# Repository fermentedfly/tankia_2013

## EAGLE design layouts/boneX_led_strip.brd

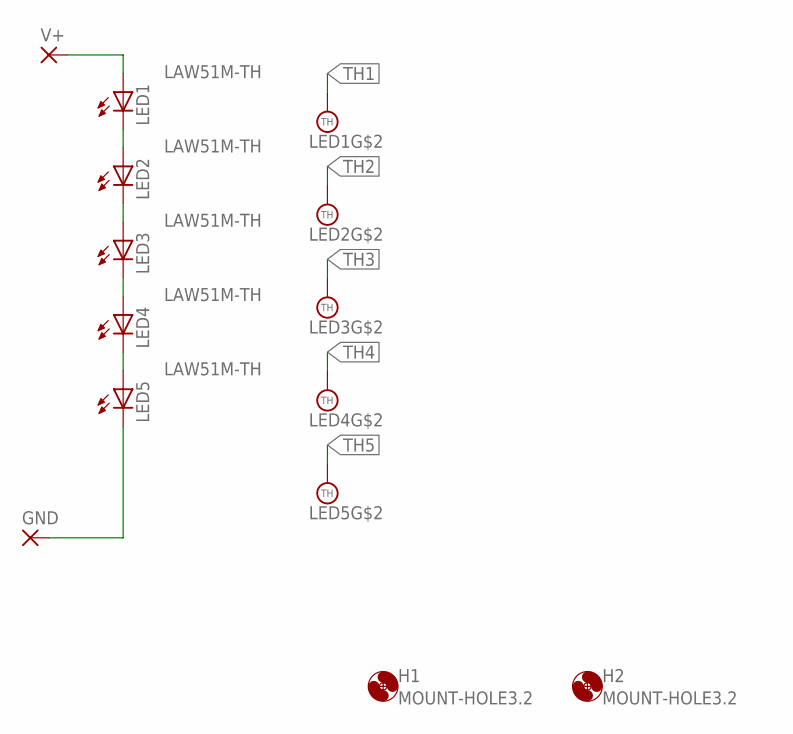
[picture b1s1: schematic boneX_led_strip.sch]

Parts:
GND: SMD5; SMD2,54-5,08
H1, H2: MOUNT-HOLE3.2; 3,2
LED1, LED2, LED3, LED4, LED5: LAW51M-TH; W51-COOL
V+: SMD5; SMD2,54-5,08

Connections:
GND: GND.1, LED5.C
unnamed: LED4.C, LED5.A
unnamed: LED3.C, LED4.A
unnamed: LED2.C, LED3.A
unnamed: LED1.C, LED2.A
TH1: LED1.TH@1 (TH), LED1.TH@2 (TH), LED1.TH@3 (TH), LED1.TH@4 (TH), LED1.TH@5 (TH), LED1.TH@6 (TH), LED1.TH@7 (TH), LED1.TH@8 (TH), LED1.TH@9 (TH), LED1.TH@10 (TH), LED1.TH@11 (TH), LED1.TH@12 (TH)
TH2: LED2.TH@1 (TH), LED2.TH@2 (TH), LED2.TH@3 (TH), LED2.TH@4 (TH), LED2.TH@5 (TH), LED2.TH@6 (TH), LED2.TH@7 (TH), LED2.TH@8 (TH), LED2.TH@9 (TH), LED2.TH@10 (TH), LED2.TH@11 (TH), LED2.TH@12 (TH)
TH3: LED3.TH@1 (TH), LED3.TH@2 (TH), LED3.TH@3 (TH), LED3.TH@4 (TH), LED3.TH@5 (TH), LED3.TH@6 (TH), LED3.TH@7 (TH), LED3.TH@8 (TH), LED3.TH@9 (TH), LED3.TH@10 (TH), LED3.TH@11 (TH), LED3.TH@12 (TH)
TH4: LED4.TH@1 (TH), LED4.TH@2 (TH), LED4.TH@3 (TH), LED4.TH@4 (TH), LED4.TH@5 (TH), LED4.TH@6 (TH), LED4.TH@7 (TH), LED4.TH@8 (TH), LED4.TH@9 (TH), LED4.TH@10 (TH), LED4.TH@11 (TH), LED4.TH@12 (TH)
TH5: LED5.TH@1 (TH), LED5.TH@2 (TH), LED5.TH@3 (TH), LED5.TH@4 (TH), LED5.TH@5 (TH), LED5.TH@6 (TH), LED5.TH@7 (TH), LED5.TH@8 (TH), LED5.TH@9 (TH), LED5.TH@10 (TH), LED5.TH@11 (TH), LED5.TH@12 (TH)
V+: LED1.A, V+.1

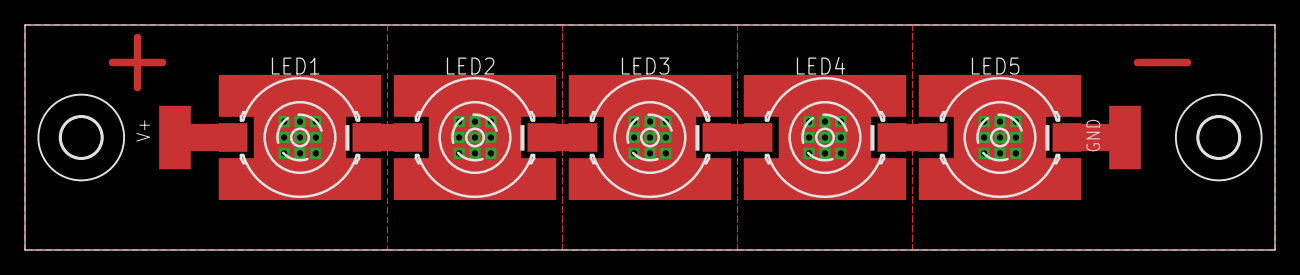
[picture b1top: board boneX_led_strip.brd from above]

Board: 2 copper layers, 100.0 x 18.0 mm, 9 parts (0 on the bottom side), 11 nets.

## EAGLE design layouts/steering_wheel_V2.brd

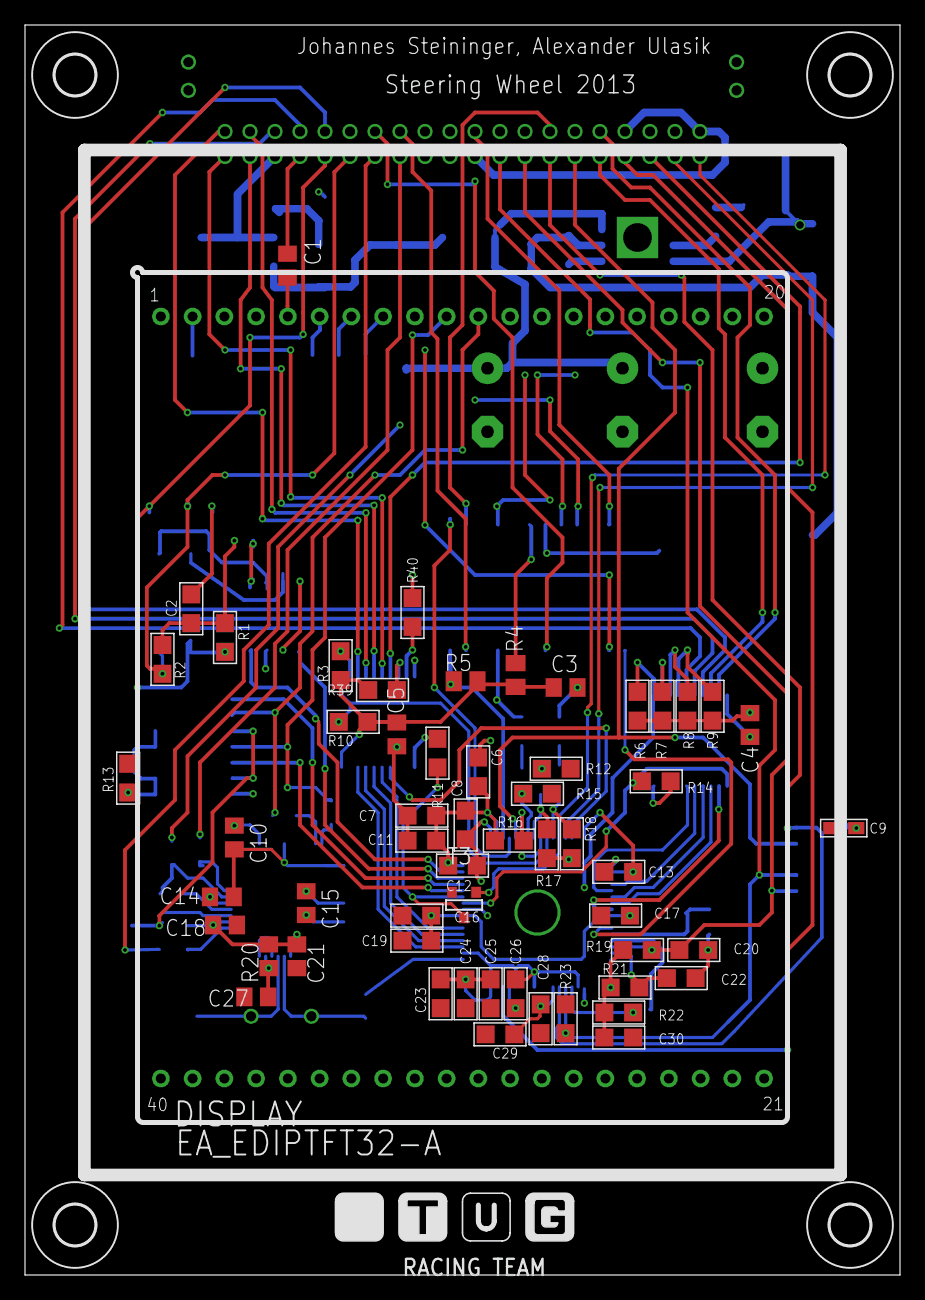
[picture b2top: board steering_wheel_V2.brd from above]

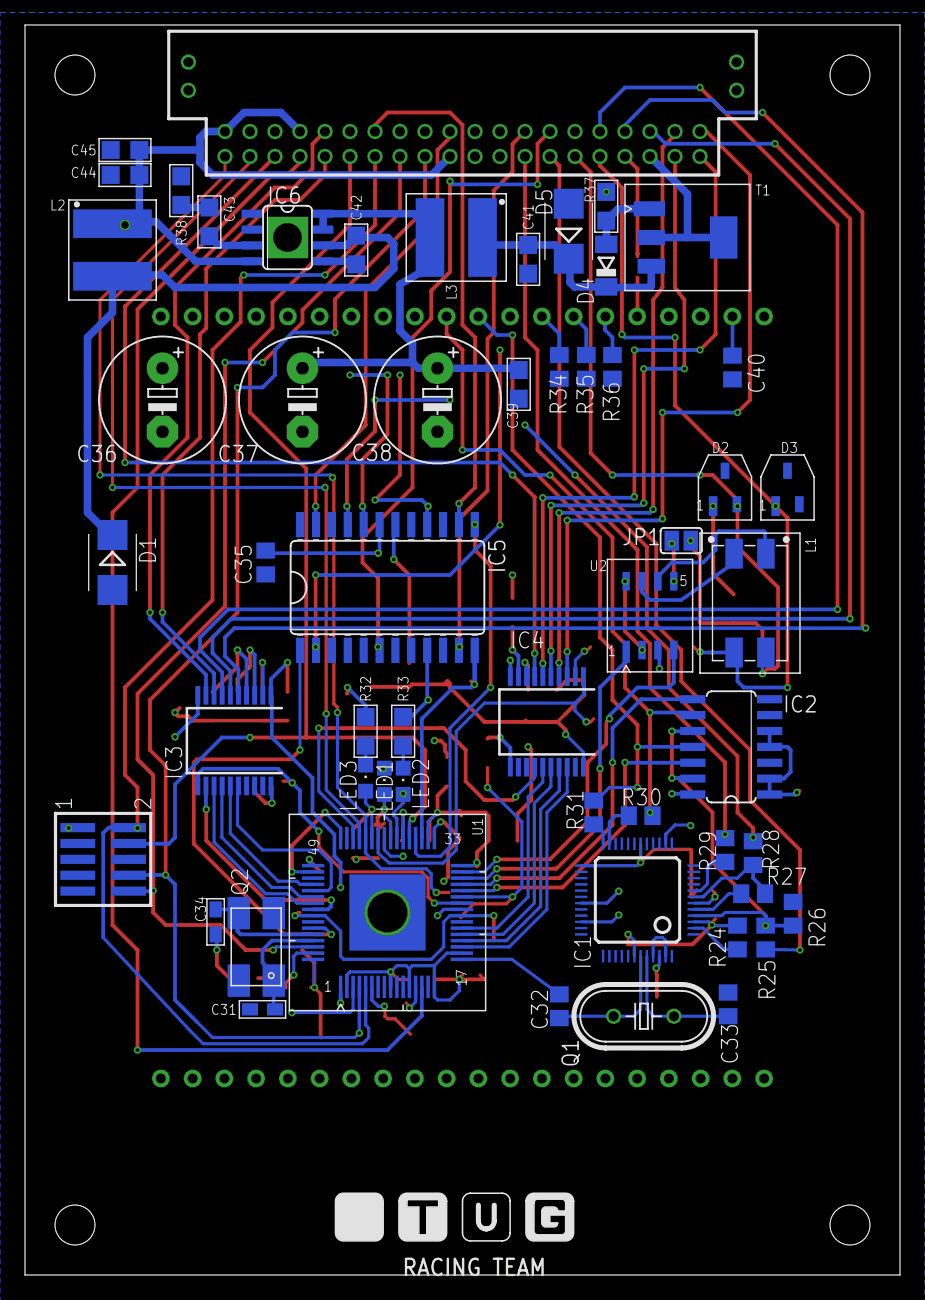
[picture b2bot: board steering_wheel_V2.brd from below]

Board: 4 copper layers, 70.0 x 100.0 mm, 122 parts (56 on the bottom side), 103 nets.

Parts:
C1, C3, C4, C5, C10, C15, C18, C21, C27: 100n; C0805
C2, C25, C45: 10n; 2012M_0805
C6, C7, C8, C11, C12, C13, C20, C22, C24, C26, C30, C39, C41: 100n; 2012M_0805
C9: 100n; 1608M_0603
C14: 33n; C0805
C16, C17, C19: 470n; 2012M_0805
C23, C42, C44: 220n; 2012M_0805
C28, C29: 1u; 2012M_0805
C31, C34: 33p; 1608M_0603
C32, C33: 68p; C0805
C35, C40: 1u; C0805
C36: 100u; E5-10,5
C37, C38: 50u; E5-10,5
C43: 22n; 2012M_0805
CON1: SAMTEC_DAP; FTSH-105-01-XXX-DV-K
D1: MBRS130LT3; SMB
D2, D3: ESD24VS2U; SOT23-3
D4: BZV55/C13; SOD80C
D5: 1SMB30AT3; SMB
DISPLAY: EA_EDIPTFT32-A; EDIPTFT32-A
FRAME1, FRAME2, FRAME3, FRAME5: A4L-LOC-RACING-NOLOGO; NOLOGO
FRAME4, FRAME6: A4L-LOC-RACING-BRD-TPLACE; LOGO_RACING_BRD_TPLACE
H1, H2, H3, H4: MOUNT-HOLE3.2; 3,2
IC1: FT2232; LQFP48
IC2: 74AC125D; SO14
IC3, IC4: MAX6818; SSOP20
IC5: MAX7221; SO_W24
IC6: TLE8366E V50; SOIC08-II
J1: T2M-120-01-L-D-RA-WT
JP1: SJ
L1: CM_51U1A; WE-SL2
L2, L3: L47UH_0.82A_744053470_WE-TPC_LH; WE-TPC_LH
LED1, LED2, LED3: CHIPLED_0805
Q1: 6MHz; HC49U70
Q2: 8Mhz; ABMM2
R1, R2: 1k5; 2012M_0805
R3, R6, R7, R8, R9, R10, R11, R13, R14, R15, R16, R17, R18, R19, R21, R22, R23, R37, R39, R40: 10k; 2012M_0805
R4: 10K; M0805
R5: 20k; M0805
R12, R33: 470; 2012M_0805
R20: 470R; R0805
R24, R26: 10k; R0805
R25: 2k7; R0805
R27: 1k5; R0805
R28, R29: 27R; R0805
R30, R31: 270; R0805
R32: 2k2; 2012M_0805
R34, R35, R36: X(10k); R0805
R38: 22k; 2012M_0805
T1: BSP613P; SOT223-3
T3: SOT-23
U1: SAK-XC2336B-40F80L; PG-LQFP-64-6
U2: TLE6251DS; SO8

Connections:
!PORST: C20.2, CON1.10, J1.15, R19.1, U1.62
!TRST: CON1.8, J1.17, R23.1, U1.4
!U0C1_SEL0: IC5.12, R5.1, U1.35
+5V/1#: C1.1, C3.1, C4.2, C5.2, C6.2, C7.2, C8.2, C9.2, C10.1, C11.1, C12.2, C13.2, C15.1, C18.1, C21.1, C23.2, C24.2, C25.2, C26.2, C30.2, C35.1, C36.+, C40.1, C44.2, C45.2, CON1.1, DISPLAY.P$2, DISPLAY.P$5, DISPLAY.P$22, IC1.3, IC1.14, IC1.31, IC1.42, IC2.14, IC3.20, IC4.20, IC5.19, IC6.4, J1.2, J1.8, J1.19, L2.1, R3.2, R4.1, R5.2, R6.1, R7.1, R8.2, R9.2, R10.1, R14.1, R16.1, R19.2, R20.2, R21.2, R22.2, R24.2, R39.2, R40.2, U1.2, U1.9, U1.12, U1.16, U1.18, U1.32, U1.34, U1.48, U1.50, U1.64, U2.3
BUTTON_PUSHED_1: IC3.11, R14.2, U1.26
BUTTON_PUSHED_2: R11.2, T3.1, U1.27
BUT_MIN: IC3.16, U1.53
BUT_PLUS: IC3.12, U1.56
BUT_TL: IC3.14, U1.54
CAN0_HIGH: D3.1, J1.31, L1.3, R1.1
CAN0_LOW: D2.2, J1.29, L1.2, R2.1
CAN0_RXD: U1.31, U2.4
CAN0_TXD: U1.30, U2.1
DAP0: CON1.4, J1.11, U1.37
DAP1: CON1.2, J1.13, U1.5
DD_5: IC4.14, U1.46
DD_PIN3: J1.1, T3.3, U1.44
DD_PIN4: J1.3, U1.45
DD_PIN5: IC4.7, J1.5
DIG0: IC5.2, J1.24
DIG1: IC5.11, J1.26
DIG2: IC5.6, J1.28
EEDATA: IC1.2, R24.1
ENCODER_1: IC4.3, J1.40
ENCODER_2: IC4.4, J1.38
ENCODER_4: IC4.5, J1.37
ENCODER_8: IC4.6, J1.39
ENC_1: IC4.18, U1.19
ENC_2: IC4.17, U1.20
ENC_4: IC4.16, U1.21
ENC_8: IC4.15, U1.22
EN_PB_1: IC3.1, R6.2, U1.25
EN_PB_2: IC4.1, R10.2, U1.42
GND: C1.2, C2.2, C3.2, C4.1, C5.1, C6.1, C7.1, C8.1, C9.1, C10.2, C11.2, C12.1, C13.1, C14.1, C15.2, C16.2, C17.2, C18.2, C19.2, C20.1, C21.2, C22.1, C23.1, C24.1, C25.1, C26.1, C27.1, C28.2, C29.2, C30.1, C31.2, C32.1, C33.1, C34.2, C35.2, C36.-, C37.-, C38.-, C39.1, C40.2, C41.1, C44.1, C45.1, CON1.3, CON1.5, CON1.9, D1.A, D2.1, D3.2, D5.A, DISPLAY.P$1, DISPLAY.P$21, IC1.9, IC1.18, IC1.25, IC1.34, IC1.45, IC1.47, IC2.7, IC3.10, IC4.10, IC5.4, IC5.9, IC6.1, IC6.2, IC6.HS, J1.4, J1.6, J1.12, J1.21, J1.30, J1.33, R12.2, R13.2, R15.1, R17.1, R18.1, R23.2, R26.1, R32.2, R33.2, R34.1, R35.1, R36.1, R37.1, R38.1, T3.2, U1.1, U1.13, U1.17, U1.33, U1.49, U1.PAD, U2.2, U2.8
LVPD_SUP: J1.35, T1.2, T1.TAB
MINUS: IC3.5, J1.34
unnamed: C31.1, Q2.1, U1.61
unnamed: C34.1, Q2.3, U1.60
unnamed: C14.2, IC1.6
unnamed: R22.1, U1.3
unnamed: IC4.8, R39.1
unnamed: C16.1, C17.1, C19.1, U1.24, U1.41, U1.57
unnamed: C22.2, R21.1, U1.63
unnamed: DISPLAY.P$8, R34.2
unnamed: C28.1, C29.1, U1.6
unnamed: DISPLAY.P$7, R35.2
unnamed: IC1.8, R29.2
unnamed: IC1.7, R27.1, R28.2
unnamed: DISPLAY.P$6, R36.2
unnamed: IC1.5, R27.2
unnamed: C27.2, IC1.46, R20.1
unnamed: L1.4, U2.7
unnamed: L1.1, U2.6
unnamed: IC1.24, R31.1
unnamed: IC1.23, R30.1
unnamed: C32.2, IC1.43, Q1.2
unnamed: C33.2, IC1.44, Q1.1
unnamed: JP1.1, U2.5
unnamed: C37.+, C38.+, C39.2, IC6.7, IC6.8, L3.2
unnamed: LED1.C, R12.1
unnamed: IC5.18, R4.2
unnamed: LED2.C, R33.1
unnamed: LED3.A, R18.2, U1.43
unnamed: IC2.1, IC2.2, IC2.4, IC2.5, R13.1
unnamed: IC4.2, R3.1
unnamed: C43.1, R38.2
unnamed: IC4.9, R40.1
unnamed: LED3.C, R32.1
unnamed: IC3.2, R7.2
unnamed: D4.A, R37.2, T1.1
unnamed: IC4.11, R11.1
unnamed: C43.2, IC6.3
unnamed: C42.2, D1.C, IC6.6, L2.2
unnamed: C42.1, IC6.5
unnamed: C2.1, JP1.2, R1.2, R2.2
unnamed: IC3.3, R8.1
unnamed: IC3.4, R9.1
PLUS: IC3.9, J1.10
POTI_1: J1.7, U1.14
RXD_DISP: DISPLAY.P$10, IC2.11, R31.2
SEG_A: IC5.14, J1.14
SEG_B: IC5.16, J1.16
SEG_C: IC5.20, J1.18
SEG_D: IC5.23, J1.20
SEG_E: IC5.21, J1.22
SHIFT_DOWN: IC3.6, J1.36
SHIFT_UP: IC3.8, J1.9
SH_DN: IC3.15, U1.52
SH_UP: IC3.13, U1.55
STATUS_0: R16.2, U1.38
STATUS_1: LED2.A, R15.2, U1.39
STATUS_2: LED1.A, R17.2, U1.40
SUP6.1: C41.2, D4.C, D5.C, L3.1, T1.3
TOP_LEFT: IC3.7, J1.32
TXD_DISP: DISPLAY.P$11, IC2.9, R30.2
U0C0_RXD: IC2.8, U1.29
U0C0_TXD: IC2.12, U1.28
U0C1_CLK: IC5.13, U1.36
U0C1_TXD: IC5.1, U1.59
USB_2: J1.25, R29.1
USB_3: J1.23, R28.1
USB_PWR: IC1.4, IC2.10, IC2.13, R25.1, R26.2
USB_VDD: J1.27, R25.2

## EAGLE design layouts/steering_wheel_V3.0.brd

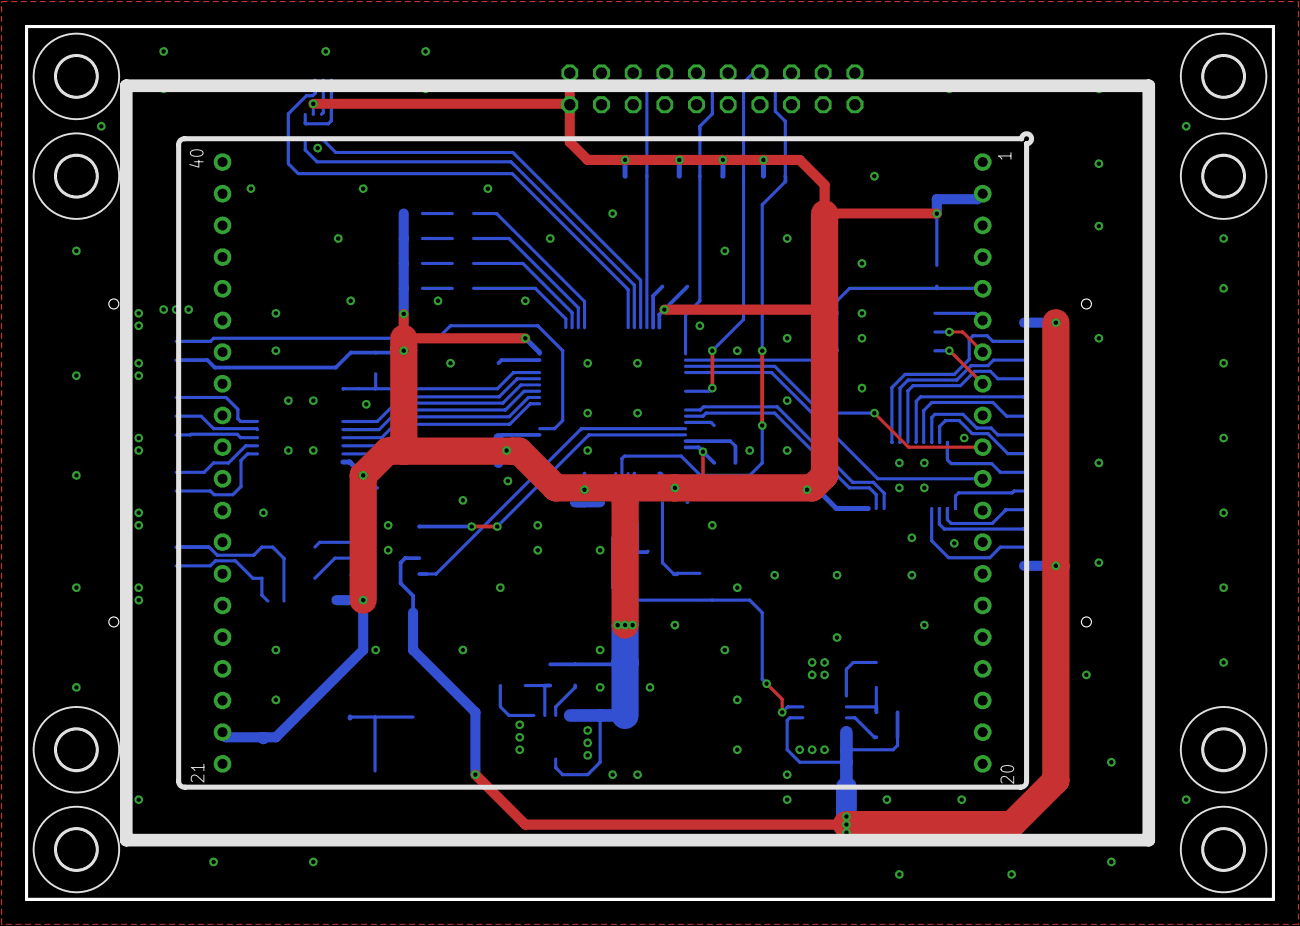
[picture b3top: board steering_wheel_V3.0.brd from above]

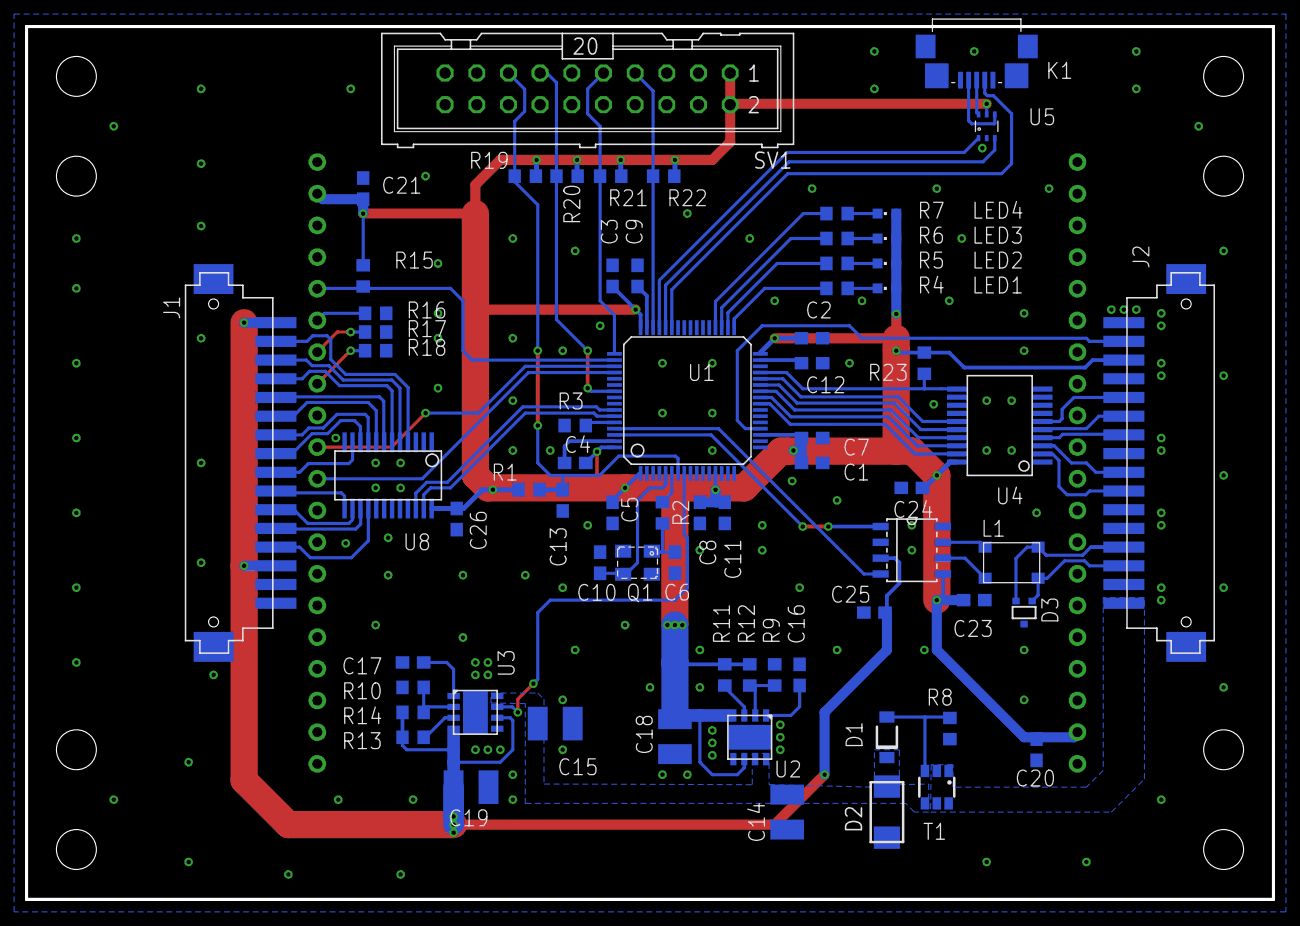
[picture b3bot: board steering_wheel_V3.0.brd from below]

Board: 2 copper layers, 100.0 x 70.0 mm, 78 parts (69 on the bottom side), 74 nets.

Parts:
C1: 4u7; C0603
C2, C3, C4, C5, C7, C13, C20, C21, C23, C24, C25, C26: 100n; C0603
C6, C10: 10p; C0603
C8: 1u; C0603
C9, C12: 2u2; C0603
C11: 10n; C0603
C14, C15, C18, C19: 22u; C1210
C16, C17: 3n3; C0603
D1: BZT52B18-E3-18; SOD123F
D2: SMA6J33CA-TR; DO214AC
D3: PESD1CAN-U; SOT-323
DISPLAY: EA_EDIPTFT32-A; EDIPTFT32-A
H1, H2, H3, H4, H5, H6, H7, H8: MOUNT-HOLE3.2; 3,2
J1, J2: 1-292227-6
K1: USB-MICROZX62R-B; ZX62R-B
L1: ACT45B
LED1, LED2, LED3, LED4: CHIPLED_0603
Q1: 25 MHz; 3.2X2.5MM-SMD
R1, R8, R11, R13, R23: 10k; R0603
R2: 390; R0603
R3: 4k7; R0603
R4, R5, R6, R7: 470; R0603
R9: 383k; R0603
R10: 44.2k; R0603
R12: 1M21; R0603
R14: 232k; R0603
R15: 100k; R0603
R16, R17, R18: X(10k); R0603
R19: x(10K); R0603
R20, R21, R22: 10K; R0603
SV1: ML20
T1: FDC5614P; SSOT6
U1: STM32F415RG; LQFP64
U2, U3: LMZ21701; SIL0008E
U4: MAX6818; SSOP-20
U5: NUF2221; SOT363
U6: SN65HVD256; SOIC8
U8: MAX7313AEG+; QSOP-24

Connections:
!MAX_CH: R23.1, U1.29, U4.11
!RESET: C13.1, R1.2, R19.2, SV1.15, U1.7
+3V3: C1.1, C2.1, C3.1, C4.1, C5.1, C7.1, C8.1, C11.1, C18.1, C20.1, C21.1, C23.2, C24.2, C26.2, DISPLAY.P$2, DISPLAY.P$22, J2.14, LED1.A, LED2.A, LED3.A, LED4.A, R1.1, R11.2, R12.2, R15.1, R19.1, R20.1, R21.1, R22.1, R23.2, SV1.1, SV1.2, U1.1, U1.13, U1.19, U1.32, U1.48, U1.64, U2.4, U2.6, U4.20, U5.5, U6.P5, U8.24
+5V: C19.1, C25.2, J1.1, J1.14, R13.2, R14.2, U3.4, U3.6, U6.P3
ADC1_IN4: J2.15, U1.20
CAN1_RX: U1.61, U6.P4
CAN1_TX: U1.62, U6.P1
CAN_HIGH: D3.2, J2.4, L1.4
CAN_LOW: D3.1, J2.3, L1.3
DISPLAY_RESET: DISPLAY.P$5, R15.2, U1.50
ENTER: J2.12, U4.6
EN_+5V: U1.8, U3.7
GND: C1.2, C2.2, C3.2, C4.2, C5.2, C6.2, C7.2, C8.2, C9.2, C10.2, C11.2, C12.2, C13.2, C14.2, C15.2, C16.2, C17.2, C18.2, C19.2, C20.2, C21.2, C23.1, C24.1, C25.1, C26.1, D2.A, D3.3, DISPLAY.P$1, DISPLAY.P$21, J1.PAD1, J1.PAD2, J2.2, J2.5, J2.6, J2.9, J2.13, J2.16, J2.PAD1, J2.PAD2, K1.GND, K1.P$6, K1.P$7, K1.P$8, K1.P$9, Q1.2, Q1.4, R3.2, R8.1, R9.1, R10.1, R16.1, R17.1, R18.1, SV1.4, SV1.6, SV1.8, SV1.10, SV1.12, SV1.14, SV1.16, SV1.18, SV1.20, U1.12, U1.18, U1.63, U2.5, U2.PAD, U3.5, U3.PAD, U4.1, U4.10, U5.2, U6.P2, U6.P8, U8.2, U8.3, U8.12, U8.21
I2C1_SCL: U1.58, U8.22
I2C1_SDA: U1.59, U8.23
LED_0: R4.1, U1.33
LED_1: R5.1, U1.34
LED_2: R6.1, U1.35
LED_3: R7.1, U1.36
LED_OIL: J1.2, U8.4
LED_RPM0: J1.3, U8.5
LED_RPM1: J1.4, U8.6
LED_RPM2: J1.5, U8.7
LED_RPM3: J1.6, U8.8
LED_RPM4: J1.7, U8.9
LED_RPM5: J1.8, U8.10
LED_RPM6: J1.9, U8.11
LED_RPM7: J1.10, U8.13
LED_RPM8: J1.11, U8.14
LED_RPM9: J1.12, U8.15
LED_WATER: J1.13, U8.16
MAX_ENTER: U1.28, U4.15
MAX_MINUS: U1.25, U4.18
MAX_PLUS: U1.27, U4.16
MAX_SHIFT_DOWN: U1.24, U4.19
MAX_SHIFT_UP: U1.26, U4.17
MINUS: J2.8, U4.3
unnamed: C9.1, U1.47
unnamed: C12.1, U1.31
unnamed: R2.1, U1.6
unnamed: C10.1, Q1.3, U1.5
unnamed: LED4.C, R7.2
unnamed: R3.1, U1.60
unnamed: DISPLAY.P$8, R18.2
unnamed: DISPLAY.P$7, R17.2
unnamed: LED2.C, R5.2
unnamed: LED3.C, R6.2
unnamed: DISPLAY.P$6, R16.2
unnamed: D1.A, R8.2, T1.3
unnamed: C6.1, Q1.1, R2.2
unnamed: LED1.C, R4.2
unnamed: C16.1, U2.1
unnamed: C17.1, U3.1
unnamed: R13.1, U3.3
unnamed: R11.1, U2.3
unnamed: R9.2, R12.1, U2.2
unnamed: R10.2, R14.1, U3.2
unnamed: L1.1, U6.P7
unnamed: L1.2, U6.P6
PLUS: J2.11, U4.5
SHIFT_DOWN: J2.7, U4.2
SHIFT_UP: J2.10, U4.4
SWCLK: R21.2, SV1.9, U1.49
SWDIO: R22.2, SV1.7, U1.46
SWO: R20.2, SV1.13, U1.55
UART4_RX: DISPLAY.P$11, U1.52
UART4_TX: DISPLAY.P$10, U1.51
USB_DM: K1.D-, U5.4
USB_DP: K1.D+, U5.6
USB_OTG_FS_DM: U1.44, U5.3
USB_OTG_FS_DP: U1.45, U5.1
USB_OTG_FS_ID: K1.ID, U1.43
VCC: C14.1, C15.1, D1.C, D2.C, T1.4, U2.7, U2.8, U3.8
V_IN: J2.1, T1.1, T1.2, T1.5, T1.6
